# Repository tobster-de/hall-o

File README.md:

Hall-O (KiCad)
==============

Based upon the original Hall-O ([look here](http://reprap.org/wiki/Hall-%CE%98)). This is a single sided board for easier home etching.

Parts list:
-----------
- SS495B hall sensor (replacement [SS495A](http://www.reichelt.de/index.html?ACTION=3;ARTICLE=151339;SEARCH=SS495))
- [LM-258-D](http://www.reichelt.de/index.html?ACTION=3&LA=5&ARTICLE=39446&GROUPID=5464&artnr=LM+258+D) op amp
- SMD [potentiometer 10K](http://www.reichelt.de/index.html?ACTION=3&LA=5&ARTICLE=146074&GROUPID=3131&artnr=23A-10K)
- 0805 [SMD resistors](https://www.reichelt.de/SMD-0805/2/index.html?ACTION=2&LA=2&GROUPID=7962) (2x 560, 1x 1K, 3x 10K, 1x 22K, 1x 1M)
- SMD [capacitor 100nF](http://www.reichelt.de/index.html?ACTION=3&LA=2&ARTICLE=31879&GROUPID=8048&artnr=X7R-G0805+100N&SEARCH=%252A)
- SMD [tantalum capacitor 10µF/16V](http://www.reichelt.de/index.html?ACTION=3&LA=446&ARTICLE=31347&GROUPID=3147&artnr=SMD+TAN.10%2F16&SEARCH=SMD%2BTAN) 
- 1206 LED ([example](http://www.reichelt.de/index.html?ACTION=3&LA=2&ARTICLE=156250&GROUPID=3035&artnr=LED+EL+1206+OR&SEARCH=%252A), blue or white requires other resistor, replace R6)
- [BC848](http://www.reichelt.de/index.html?ACTION=3&LA=5&ARTICLE=18564&GROUPID=7206&artnr=BC+848A+SMD) SMD transistor
- 1x4 angled [pin headers](http://www.reichelt.de/index.html?ACTION=3&LA=2&ARTICLE=19507&GROUPID=7434&artnr=SL+1X40W+2%2C54&SEARCH=%252A) or [connector](http://www.reichelt.de/index.html?ACTION=3&LA=5&ARTICLE=137974&GROUPID=7525&artnr=PSS+254%2F4W)
- (or solder wires directly and route wires through holes)
- in order to activate: neodym magnet

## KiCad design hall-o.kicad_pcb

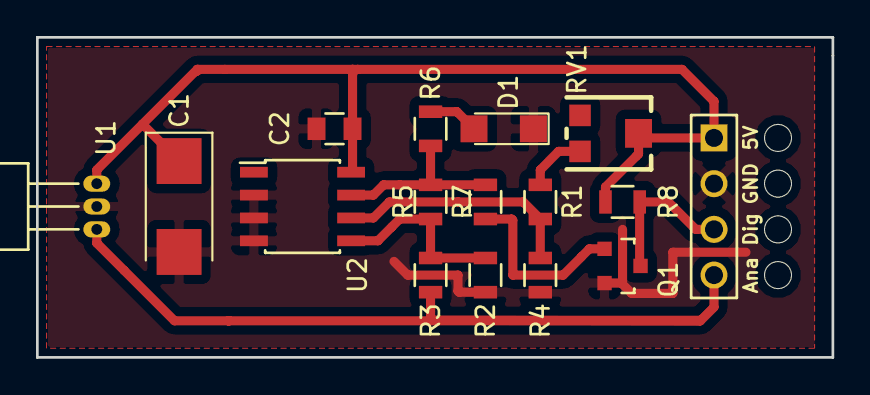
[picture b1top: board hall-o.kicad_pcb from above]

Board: 2 copper layers, 44.2 x 17.8 mm, 20 parts (0 on the bottom side), 10 nets.

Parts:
5V: MountingHole_2.2mm_M2
Ana: MountingHole_2.2mm_M2
C1: 10µF/16V; CP_Tantalum_Case-C_EIA-6032-28_Reflow
C2: 100nF; C_0805
D1: LED; LED_1206
Dig: MountingHole_2.2mm_M2
GND: MountingHole_2.2mm_M2
P1: CONN; pin_header_2.54mm_1x4
Q1: BC848; SOT-23
R1, R4, R8: 10K; R_0805
R2: 22K; R_0805
R3, R6: 560R; R_0805
R5: 1M; R_0805
R7: 1K; R_0805
RV1: 10K; 35WR
U1: SS495B; TO-92_Horizontal1_Inline_Narrow_Oval
U2: LM258D; SOIC-8_3.9x4.9mm_Pitch1.27mm

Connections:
/+5V: C1.1, C2.1, P1.1, R8.1, RV1.2, U1.1, U2.8
/GND: C1.2, C2.2, D1.1, P1.2, Q1.2, R2.1, R4.2, U1.2, U2.2, U2.3, U2.4
/SIG: P1.4, R3.1, U1.3
/STOP: P1.3, Q1.3, R8.2
unnamed: D1.2, R6.2
unnamed: Q1.1, R7.1
unnamed: R1.1, R2.2, U2.6
unnamed: R1.2, RV1.3
unnamed: R3.2, R4.1, R5.2, U2.5
unnamed: R5.1, R6.1, R7.2, U2.7

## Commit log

2016-03-25 hall-o
    remix of hall-o
2016-03-27 thickened traces
2016-03-27 renders
    added renders
2016-03-30 update gerbers
2016-05-14 hall-o
2017-01-30 single sided, rerouted
2017-01-31 update renderings
2017-01-31 larger tantalum cap
2017-01-31 cleanup
